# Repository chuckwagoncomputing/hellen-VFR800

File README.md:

bumpThis repo contains files to build a standalone plug and play RusEFI Hellen based ECU for a 99 Honda VFR800. The prototype is unfinished and currently none of these files can be used to make a functioning ECU

A quick look at the wiring diagrams suggest this hardware should also be compatible with the CBR600F4i, CBR929RR, and 01-03 CBR1100xx  if the ECU connectors were repinned.

In addition to the above it may be able to replace the ignition module/ECU of a 98-08 VT1100C, 01-07 VT750DC, 02-04 VTX1800, RC51, and 2003-09 VTX1300 with some harness repinning

Features in progress as of v0.03:

Drop in ECU replacement for 99-01 VFR800 with addition of 2 wideband oxygen sensors

4x sequential ignition/injection

CANBUS

2x Wideband oxygen sensor channels

3x lowside driver output on rear connector

Inputs for analog sensor on rear connector

USB support

Bluetooth connectivity

MicroSD card for logging

VSS input to ECU for eventual implementation of traction control

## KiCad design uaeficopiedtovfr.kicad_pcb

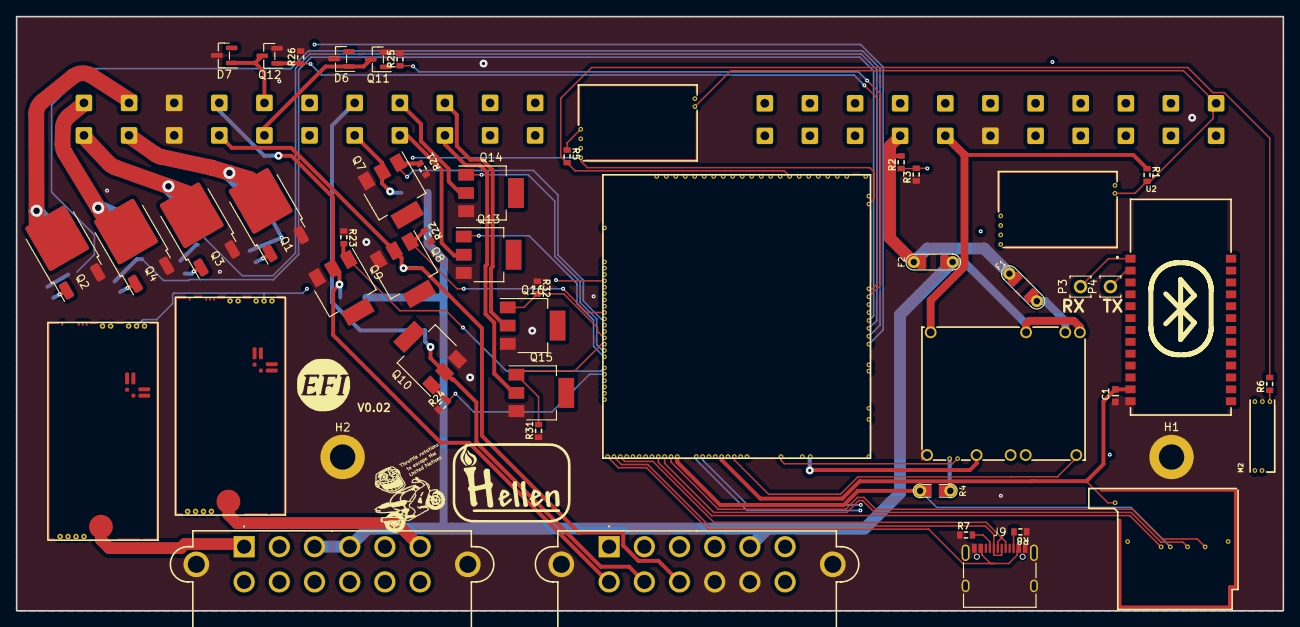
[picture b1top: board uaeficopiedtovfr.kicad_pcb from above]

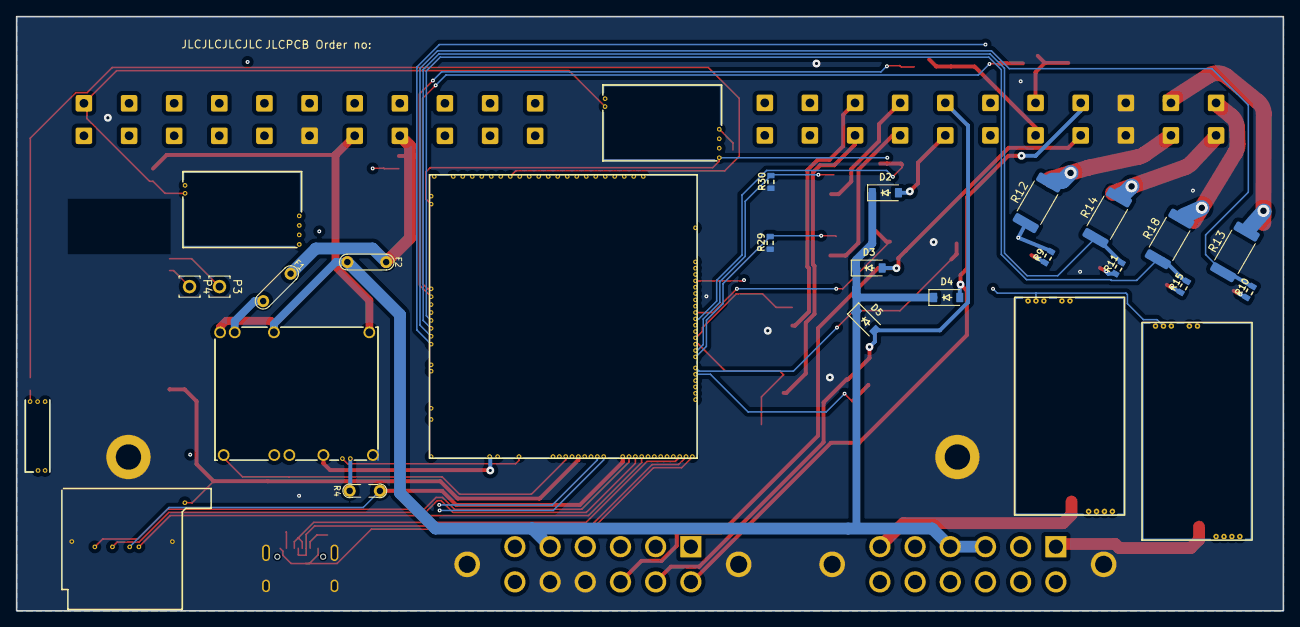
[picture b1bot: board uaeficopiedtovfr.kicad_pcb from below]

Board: 4 copper layers, 160.0 x 75.0 mm, 69 parts (14 on the bottom side), 89 nets.

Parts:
C1: 100n; C0603
D2, D3, D4, D5: B5819W; SOD-123
D6, D7: PSM712-LF; SOT-23
F1, F2: 12H1500D; PAD-1206-PAD
G3: RUSEFI_LOGO; rusefi_logo
G4: LOGO
H1, H2: MountingHole_Pad; MountingHole_3.2mm_M3_DIN965_Pad
J1, J4: DTF13-12PB; DTF1312PB
J9: USB_C_Receptacle_USB2.0; USB_C_Receptacle_XKB_U262-16XN-4BVC11
M1: Module-power_12and5V-0.2; power_12and5V
M2: Module-knock-0.2; knock
M3: Module-vr-discrete-0.4; vr-discrete
M4: Module-vr-max9924-0.1; vr-max9924
M5, M7: Module-wbo-0.5; wbo
M6: Module:mega-mcu100/0.2; mega-mcu100
M8: Module-sd-0.1; sd
P3, P4: Pad; PAD-TH
Q1, Q2, Q3, Q4: ISL9V3040D3S; TO-252-2
Q7, Q8, Q9, Q10, Q13, Q14, Q15, Q16: ZXMS6005SGTA; SOT-223
Q11, Q12: AO3400A; SOT-23
R1, R21, R22, R23, R24, R25, R26, R29, R30, R31, R32: 4.7k; R0603
R2: 33k; R0603
R3: 6.8k; R0603
R4: Jumper-Pad-Pad; PAD-0805-PAD
R5, R6: 0; R0603
R7, R8: 5.6k; R0603
R9, R10, R11, R15: 22; R0603
R12, R13, R14, R18: 0; R_2512_6332Metric
U1: VFRboardempty
U2: JDY-33
text1: trollfaceVFR

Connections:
+3.3VA: C1.2, M6.N15 (V33_SWITCHABLE), M8.V1 (V33), U2.12 (3V3)
+5V: M1.E4 (V5), M6.N22 (VCC)
+5VA: M2.E1 (V5A), M3.E4 (V5_IN), M4.E4 (V5_IN), M5.W1 (V5_IN), M6.E1 (V5A_SWITCHABLE), M6.W2 (V5A_SWITCHABLE), M7.W1 (V5_IN)
+5VP: M1.V4 (5VP), R1.1, U1.B7
+12V: F1.1, F2.1, R2.2, U1.B8
+12V_RAW: D2.1 (K), D3.1 (K), D4.1 (K), D5.1 (K), F2.2, J1.3, J1.4, J4.5, M1.V1 (V12_PERM), M1.V3 (V12_RAW)
/ADC3: M6.S15 (IN_KNOCK_(PA2)), R5.2, R6.2
/BARO: M6.S7 (IN_AUX3_(PC5)), U1.B4
/CAM+: M3.W2 (VR+), U1.B11
/CAM/CRANK-: M3.W1 (VR-), M4.W1 (VR-), R1.2, U1.B12
/CAN+: J4.7, M5.W4 (CANH), M6.W11 (CANH), M7.W4 (CANH)
/CAN-: J4.6, M5.W3 (CANL), M6.W12 (CANL), M7.W3 (CANL)
/CLT: M6.S21 (IN_CLT_(PC2)), U1.B15
/CRANK+: M4.W2 (VR+), U1.B22
/FILIGHT: D6.1, Q11.2 (D), U1.A7
/FUELPUMP_LS: D2.2 (A), Q7.2 (D), U1.A5
/IAT_SENSOR: M6.S20 (IN_IAT_(PC3)), U1.B5
/IGN1: M6.W10 (IGN1_(PC13)), R9.2, R12.1
/IGN2: M6.W9 (IGN2_(PE5)), R10.2, R13.1
/IGN3: M6.W8 (IGN3_(PE4)), R11.2, R14.1
/IGN4: M6.W7 (IGN4_(PE3)), R15.2, R18.1
/IGNOUT1: Q1.2 (C), R12.2, U1.A10
/IGNOUT2: Q2.2 (C), R13.2, U1.A21
/IGNOUT3: Q3.2 (C), R14.2, U1.A11
/IGNOUT4: Q4.2 (C), R18.2, U1.A22
/INJ1: M6.E17 (OUT_INJ1_(PD3)), Q13.1 (G), R29.2
/INJ2: M6.E16 (OUT_INJ2_(PA9)), Q14.1 (G), R30.2
/INJ3: M6.E15 (OUT_INJ3_(PD11)), Q15.1 (G), R31.2
/INJ4: M6.E14 (OUT_INJ4_(PD10)), Q16.1 (G), R32.2
/INJOUT1: Q13.2 (D), U1.A4
/INJOUT2: Q14.2 (D), U1.A15
/INJOUT3: Q15.2 (D), U1.A3
/INJOUT4: Q16.2 (D), U1.A14
/INTAKEFLAP: D5.2 (A), J4.11, Q10.2 (D), U1.A16
/IN_FLEX: J4.3, M6.S17 (IN_VSS_(PE11))
/IN_HALL1: M6.S4 (IN_D1_(PE12)), U1.B17
/IN_KNOCK: M2.E3 (OUT_KNOCK), R6.1
/IN_KNOCK_RAW: J4.4, M2.W1 (IN_KNOCK)
/IN_MAP: M6.S13 (IN_MAP1_(PC0)), U1.B3
/IN_TPS1: M6.S18 (IN_TPS_(PA4)), U1.B14
/IN_VIGN: F1.2, M1.V2 (IN_VIGN)
/IN_VMAIN: M6.S6 (IN_AUX4_(PA7)), R2.1, R3.2
/LS1: M6.E11 (OUT_INJ7_(PD15)), Q7.1 (G), R21.2
/LS2: M6.E10 (OUT_INJ8_(PD12)), Q8.1 (G), R22.2
/LS3: M6.E18 (OUT_PWM1_(PD13)), Q9.1 (G), R23.2
/LS4: M6.E19 (OUT_PWM2_(PC6)), Q10.1 (G), R24.2
/LS_WEAK1: M6.W4 (IGN7_(PB9)), Q11.1 (G), R25.1
/LS_WEAK2: M6.W3 (IGN8_(PE6)), Q12.1 (G), R26.1
/OUT_LS2: D3.2 (A), J4.10, Q8.2 (D), U1.A8
/OUT_LS3: D4.2 (A), J4.12, Q9.2 (D), U1.A19
/OUT_LS_WEAK2: D7.1, Q12.2 (D), U1.A18
/PG_5VP: M6.N12 (SPI3_MOSI_(PC12)), M8.V5 (SD_MOSI), R4.2
/PWR_EN: M1.E5 (EN_5VP), M6.N20 (OUT_PWR_EN_(PE10))
/USB+: J9.A6 (D+), J9.B6 (D+), M6.N3 (USBP_(PA12))
/USB-: J9.A7 (D-), J9.B7 (D-), M6.N2 (USBM_(PA11))
/VBAT: M1.E1 (VBAT), M6.N17 (VBAT)
/VBUS: J9.A4 (VBUS), J9.A9 (VBUS), J9.B4 (VBUS), J9.B9 (VBUS), M6.N1 (VBUS)
/VIGN: M1.E3 (VIGN), M6.E5 (IN_VIGN_(PA5))
/VR1: M3.E3 (OUT), M6.N18 (UART8_RX_(PE0))
/VR1_A: M3.E2 (OUT_A), R5.1
/VR1_THRESHOLD: M3.E1 (Thresh_IN), M6.E23 (OUT_PWM6_(PD14))
/VR2: M4.E3 (OUT), M6.N19 (UART8_TX_(PE1))
/VREF1: M2.W2 (VREF), M6.S22 (VREF1)
/WBO2_Heater: J1.1, M7.E5 (LSU_H+)
/WBO2_Ip: J1.11, M7.E3 (LSU_Ip)
/WBO2_Rtrim: J1.2, M7.E4 (LSU_Rtrim)
/WBO2_Un: J1.10, M7.E1 (LSU_Un)
/WBO2_Vm: J1.12, M7.E2 (LSU_Vm)
/WBO_Heater: J1.6, M5.E5 (LSU_H+)
/WBO_Ip: J1.8, M5.E3 (LSU_Ip)
/WBO_Rtrim: J1.5, M5.E4 (LSU_Rtrim)
/WBO_Un: J1.9, M5.E1 (LSU_Un)
/WBO_Vm: J1.7, M5.E2 (LSU_Vm)
GND: C1.1, D6.2, D7.2, H1.1, H2.1, J1.MH1, J1.MH2, J4.8, J4.9, J4.MH1, J4.MH2, J9.A1 (GND), J9.A12 (GND), J9.B1 (GND), J9.B12 (GND), J9.S1 (SHIELD), M1.S1 (GND), M2.E2 (GND), M3.G (GND), M4.G (GND), M5.E6 (LSU_H-), M5.G (GND), M6.G (GND), M7.E6 (LSU_H-), M7.G (GND), M8.G (GND), M8.V2 (GND), M8.V3 (GND), Q1.3 (E), Q2.3 (E), Q3.3 (E), Q4.3 (E), Q7.3 (S), Q8.3 (S), Q9.3 (S), Q10.3 (S), Q11.3 (S), Q12.3 (S), Q13.3 (S), Q14.3 (S), Q15.3 (S), Q16.3 (S), R3.1, R7.1, R8.1, R21.1, R22.1, R23.1, R24.1, R25.2, R26.2, R29.1, R30.1, R31.1, R32.1, U1.A9, U1.A20, U1.B6, U2.13 (GND)
GNDA: M6.W1 (GNDA), U1.B2
unnamed: J9.A5 (CC1), R7.2
unnamed: J9.B5 (CC2), R8.2
unnamed: M1.E6 (PG_5VP), R4.1
unnamed: M5.J1 (SEL1), M5.J_GND1 (PULL_DOWN1)
unnamed: M6.N9 (SPI3_CS_(PA15)), M8.V4 (SD_CS)
unnamed: M6.N11 (SPI3_MISO_(PC11)), M8.V7 (SD_MISO)
unnamed: M6.N10 (SPI3_SCK_(PC10)), M8.V6 (SD_SCK)
unnamed: M6.N14 (UART2_RX_(PD6)), P3.1, U2.1 (TXD)
unnamed: M6.N13 (UART2_TX_(PD5)), P4.1, U2.2 (RXD)
unnamed: M7.J1 (SEL1), M7.J_GND1 (PULL_DOWN1)
unnamed: Q1.1 (G), R9.1
unnamed: Q2.1 (G), R10.1
unnamed: Q3.1 (G), R11.1
unnamed: Q4.1 (G), R15.1

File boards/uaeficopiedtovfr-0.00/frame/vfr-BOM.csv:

Comment,Designator,Footprint,LCSC Part #
"100n","C1","C0603","C14663"
"B5819W","D2","SOD-123","C8598"
"B5819W","D3","SOD-123","C8598"
"B5819W","D4","SOD-123","C8598"
"B5819W","D5","SOD-123","C8598"
"PSM712-LF","D6","SOT-23","C32677"
"PSM712-LF","D7","SOT-23","C32677"
"12H1500D","F1","PAD-1206-PAD","C182446"
"12H1500D","F2","PAD-1206-PAD","C182446"
"RUSEFI_LOGO","G3","rusefi_logo",""
"LOGO","G4","LOGO",""
"MountingHole_Pad","H1","MountingHole_3.2mm_M3_DIN965_Pad",""
"MountingHole_Pad","H2","MountingHole_3.2mm_M3_DIN965_Pad",""
"DTF13-12PB","J1","DTF1312PB",""
"Conn_01x06","J3","PinHeader_1x06_P2.54mm_Vertical","C37208"
"DTF13-12PB","J4","DTF1312PB",""
"Conn_01x06","J6","PinHeader_1x06_P2.54mm_Vertical","C37208"
"Conn_01x05_Male","J7","Molex_SPOX_5267-05A_1x05_P2.50mm_Vertical",""
"USB_B_Mini","J8","USB-MINI-B-VERTICAL",""
"USB_C_Receptacle_USB2.0","J9","USB_C_Receptacle_XKB_U262-16XN-4BVC11","C2927038"
"Module:power_12and5V/0.2","M1","power_12and5V",""
"Module:knock/0.2","M2","knock",""
"Module:vr-discrete/0.4","M3","vr-discrete",""
"Module:vr-max9924/0.1","M4","vr-max9924",""
"Module:wbo/0.5","M5","wbo",""
"Module:mega-mcu100/0.2","M6","mega-mcu100",""
"Module:wbo/0.5","M7","wbo",""
"Pad","P1","PAD-TH",""
"Pad","P2","PAD-TH",""
"Pad","P3","PAD-TH",""
"Pad","P4","PAD-TH",""
"ISL9V3040D3S","Q1","DPAK",""
"ISL9V3040D3S","Q2","DPAK",""
"ISL9V3040D3S","Q3","DPAK",""
"ISL9V3040D3S","Q4","DPAK",""
"ZXMS6005SGTA","Q7","SOT-223","C174042"
"ZXMS6005SGTA","Q8","SOT-223","C174042"
"ZXMS6005SGTA","Q9","SOT-223","C174042"
"ZXMS6005SGTA","Q10","SOT-223","C174042"
"AO3400A","Q11","SOT-23"," C20917"
"AO3400A","Q12","SOT-23"," C20917"
"ZXMS6005SGTA","Q13","SOT-223","C174042"
"ZXMS6005SGTA","Q14","SOT-223","C174042"
"ZXMS6005SGTA","Q15","SOT-223","C174042"
"ZXMS6005SGTA","Q16","SOT-223","C174042"
"4.7k","R1","R0603",""
"33k","R2","R0603","C4216"
"6.8k","R3","R0603","C23212"
"Jumper-Pad-Pad","R4","PAD-0805-PAD","C17477"
"0","R5","R0603",""
"0","R6","R0603","C21189"
"5.6k","R7","R0603","C23189"
"5.6k","R8","R0603","C23189"
"22","R9","R0603","C23345"
"22","R10","R0603","C23345"
"22","R11","R0603","C23345"
"0","R12","R2512","C25469"
"0","R13","R2512","C25469"
"0","R14","R2512","C25469"
"22","R15","R0603","C23345"
"0","R18","R2512","C25469"
"4.7k","R21","R0603","C23162"
"4.7k","R22","R0603","C23162"
"4.7k","R23","R0603","C23162"
"4.7k","R24","R0603","C23162"
"4.7k","R25","R0603","C23162"
"4.7k","R26","R0603","C23162"
"4.7k","R29","R0603","C23162"
"4.7k","R30","R0603","C23162"
"4.7k","R31","R0603","C23162"
"4.7k","R32","R0603","C23162"
"~","text1","trollfaceVFR",""
"~","U1","VFRboardempty",""
"JDY-33","U2","JDY-33",""

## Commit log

2023-12-28 Update revision.txt
    Added name and rev 0.00
2023-12-28 renamed board to uaEFIVFR so the script runs
2023-12-28 copied project folder over to git folder
    I am not good with computer
2023-12-28 Added origin for drill file
2023-12-28 [skip actions] Auto-generated board
2023-12-28 deleted junk files
2023-12-28 changed BOM filename
2023-12-28 Re-added graphics to board
2023-12-28 removed old gerbers
2023-12-28 reuploading revision.txt
2023-12-28 i am not gud with computer
2023-12-28 added ref to graphics
2023-12-28 Changed drill origin
    Previous file had all the modules offset vertically, moved the drill location from the corner of the board to below the deutsch connectors to see if that fixed it
2023-12-28 Moved drill file again
    last commit offset it 25mm in the opposite direction
2023-12-28 Added mounting holes
2023-12-28 generate 4 layer board
2023-12-28 Added SD card support, cleaned up ignition traces
2023-12-28 forgot to increment the BOM yet again
2023-12-28 adding jlcpcb order number to silkscreen
2023-12-29 removed DNP from ignition drivers
2023-12-29 deleted old boards
2023-12-29 board still isn't exporting with ignition drivers for some reason
2023-12-29 Added board art
    I hate the antichrist
2023-12-29 Removed board art
    filling the entire backside with 0.4mm tall text made the gerbers over 100MB
2023-12-30 Fixed error on connector pinout
2023-12-30 Routed B10 and B21 to button inputs 1 and 2
    These have something to do with killing the engine if you put it in gear with the kickstand down or try to start it in gear with the kickstand down
2023-12-30 moved a VR sensor trace slightly farther away from a CANBUS thru hole
2023-12-31 Changed two deutsch connectors to single ampseal
    I did some fitment tests and decided a single big connector dead center in the board will fit the best
2023-12-31 Changed rear connector to single ampseal
    I did some fitment tests on my bike and a single rear connector in the center of the board will be far easier to fit
2023-12-31 Moved drill file
    board is generating with offset modules again
2023-12-31 Moved drill again
    Offset still exists
2023-12-31 Added art to board, updated README
    Included other potential ECU applications in readme and added some ♂art♂ to the front silkscreen
2023-12-31 Updated README.md
    More complete description of features and potential applications
2023-12-31 Added indicator for drill origin
    there was still an offset lol
2023-12-31 THERE'S STILL AN OFFSET
    Moved drill origin to left corner of main board area, if it's in line with the protrusion for the rear connector all hellen modules end up with an offset equal to 5mm or however far that sticks out
2023-12-31 Moved drill origin
    Moved drill origin Moved drill origin Moved drill origin Moved drill origin Moved drill origin Moved drill origin Moved drill origin Moved drill origin Moved drill origin Moved drill origin Moved dri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
2023-12-31 Drill file
    MY INSTINCTS SAY LIFE SHOULDN'T BE THIS HORRIBLE
2023-12-31 forgot to clear old gerbers
2023-12-31 Drill origin experiments
2023-12-31 Drill origin
    uoidhfilsuhdfiushdfuisbdf
2023-12-31 Drill origin getting closer
    dfisudhfuishdfuishdf
2023-12-31 Drill origin
    X is aligned now this should align Y
2024-01-01 Removed redundant SD card, moved rear connector inwards
2024-01-01 Fixed edge not being closed
2024-01-02 Beefed up 12V rail
2024-01-02 Routed aux2 and button3 to rear connector
    Routed aux2 and button3 to rear connector
2024-01-03 Routed button3 and aux2 inputs to rear connector
2024-01-05 swapped left and right connectors
    Had the wrong idea about what was the A vs B connector, board needs routing finished
2024-01-05 routed more connections
2024-01-05 Finished routing
2024-01-05 Finished routing (for real)
    Forgot a ground
2024-01-05 Fixed routing
    Moved trace that was routed through the MCU footprint
2024-01-06 Revert "Create .gitignore"
    This reverts commit 26cfa5cf8f53e85ffd5f3db8fd12f5310c3d0340.
2024-01-06 Revert "Merge branch 'master' of https://github.com/VFRenjoyer/hellen-VFR800"
    This reverts commit 55b484720920c2f59454420a7e030c13d3190a57, reversing
    changes made to 5f9ad006efecef1979d649e5e48fa4e9a59aecf5.
2024-01-06 death to github
2024-01-06 asdkapijds;oisiufdg
2024-01-08 Routed AUX1 input to back connector
    RIP knock sensor option
2024-01-15 Modified routing, added art
2024-01-19 Corrected 12V not being connected to A5, removed unused lowside driver
2024-01-20 Revert "Corrected 12V not being connected to A5, removed unused lowside driver"
    This reverts commit b6bd63c4784d258af73e442f4c1ae07db6db8b04.
2024-02-11 Added jumpers for power to BT module and both WBO modules
2024-02-11 removed silkscreen overlap
2024-02-13 fixed rear connector position, made USB more practical
    Rounded off corners, changed USB connector, moved AMPSeal connector closer to board edge, changed some routing
2024-02-13 Silkscreen fix
    Fixed R2 floating in space
2024-02-15 Update uaeficopiedtovfr.kicad_pcb
    changed routing, added vias to ground spurs
2024-02-16 touched up routing
2024-02-17 last one didn't save?
2024-02-17 Moved some traces
    clearance paranoia
2024-02-17 Stitched ground plane
2024-04-11 0.04 revB begins
    Added pullup resistor so tach works
2024-04-12 Moved weak LS drivers to bottom side of board
2024-04-12 made routing more beautiful
2024-04-12 added dimensions for holes and things
2024-04-14 scripts couldn't find schematic?
2024-04-17 test kicad 8
2024-04-17 [skip actions] Auto-generated board v2.1
